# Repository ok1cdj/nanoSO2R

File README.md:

# nanoSO2R
NanoSO2R box by OK1CDJ - keep it simple stupid

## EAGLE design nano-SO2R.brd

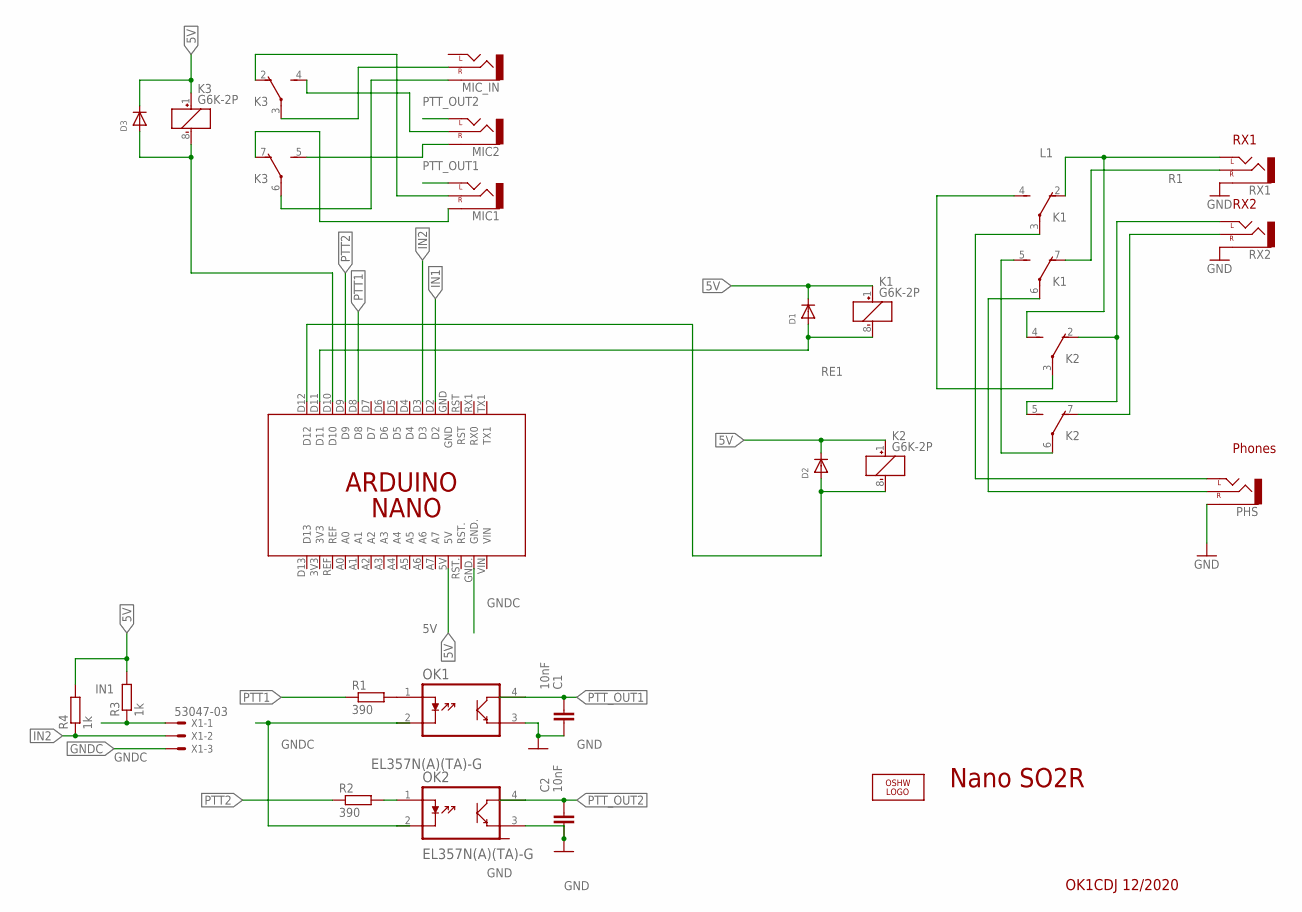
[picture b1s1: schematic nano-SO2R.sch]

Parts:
C1, C2: 10nF; C0805
D1, D2, D3: DIODESOD-323F; SOD-323F
K1, K2, K3: G6K-2P
LOGO1: OSHW_LOGO_FILLX0150-NT; OSHW_FILLX150_NOTEXT
MIC1: MIC1; AUDIO-JACK
MIC2: AUDIO-JACKPTH; AUDIO-JACK
MIC_IN: AUDIO-JACKPTH; AUDIO-JACK
OK1, OK2: EL357N(A)(TA)-G; SOP254P700X200-4N
PCB1: ARDUINO_NANO
PHS: AUDIO-JACKPTH; AUDIO-JACK
R1, R2: 390; M0805
R3, R4: 1k; M0805
RX1, RX2: AUDIO-JACKPTH; AUDIO-JACK
X1: 53047-03

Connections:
5V: D1.C, D2.C, D3.C, K1.1 (+), K2.1 (+), K3.1 (+), PCB1.5V, R3.2, R4.2
GND: C1.2, C2.2, OK1.3 (E), OK2.3 (E), PHS.SLEEVE, RX1.SLEEVE, RX2.SLEEVE
GNDC: OK1.2 (K), OK2.2 (K), PCB1.GND., X1.3
IN1: PCB1.D2, R3.1, X1.1
IN2: PCB1.D3, R4.1, X1.2
L1: K1.2 (O), K2.4 (S), RX1.TIP (LEFT)
unnamed: D3.A, K3.8 (-), PCB1.D10
unnamed: K3.3, MIC_IN.RING (RIGHT)
unnamed: K3.6, MIC_IN.SLEEVE
unnamed: K2.2 (O), K2.5 (S), RX2.TIP (LEFT)
unnamed: K2.7 (O), RX2.RING (RIGHT)
unnamed: K1.3, PHS.TIP (LEFT)
unnamed: K1.6, PHS.RING (RIGHT)
unnamed: K1.4 (S), K2.3
unnamed: K1.5 (S), K2.6
unnamed: K3.2 (O), MIC1.RING (RIGHT)
unnamed: OK2.1 (A), R2.2
unnamed: K3.7 (O), MIC1.SLEEVE
unnamed: K3.5 (S), MIC2.SLEEVE
unnamed: K3.4 (S), MIC2.RING (RIGHT)
unnamed: OK1.1 (A), R1.2
PTT1: PCB1.D8, R1.1
PTT2: PCB1.D9, R2.1
PTT_OUT1: C1.1, MIC1.TIP (LEFT), OK1.4 (C)
PTT_OUT2: C2.1, MIC2.TIP (LEFT), OK2.4 (C)
R1: K1.7 (O), RX1.RING (RIGHT)
RE1: D1.A, K1.8 (-), PCB1.D11
RE2: D2.A, K2.8 (-), PCB1.D12

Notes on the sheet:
Nano SO2R
RX2
RX1
OK1CDJ 12/2020
Phones

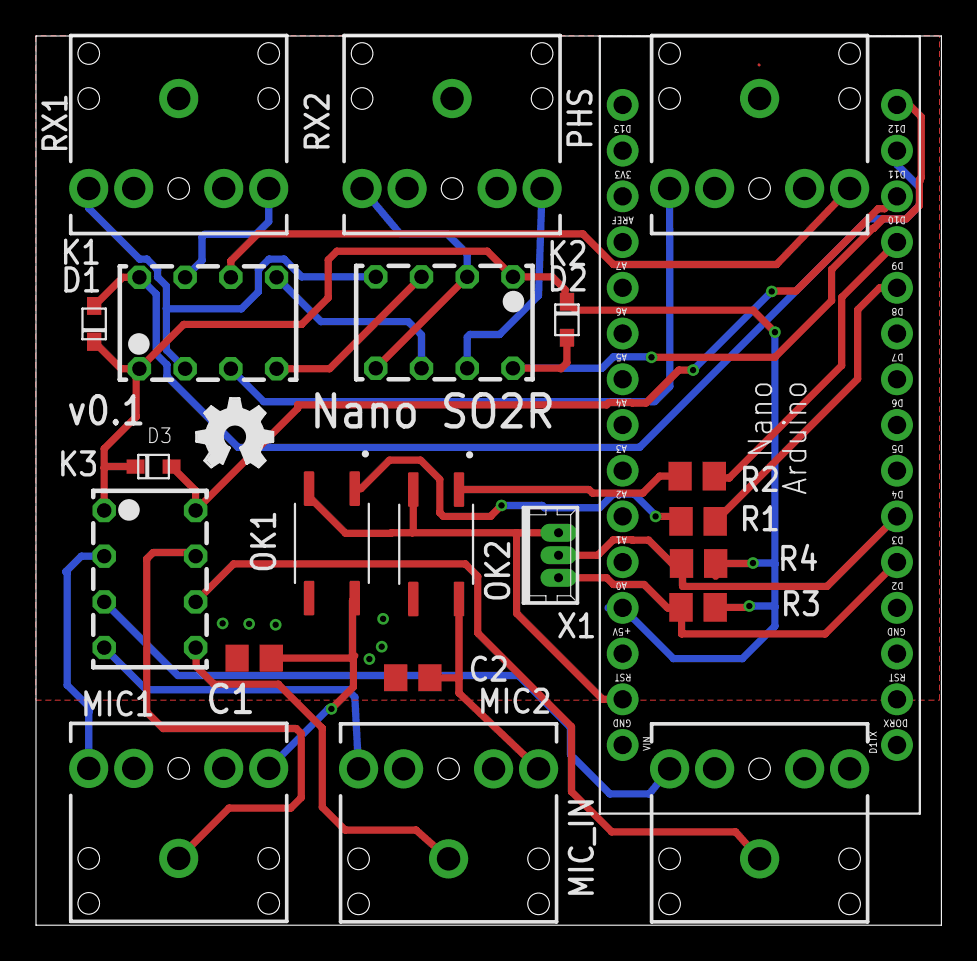
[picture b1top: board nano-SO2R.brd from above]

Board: 2 copper layers, 50.3 x 49.4 mm, 23 parts (0 on the bottom side), 28 nets.

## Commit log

2021-09-09 Arduino source code
2021-09-09 Schematic
2021-09-09 Schematic update
2021-09-09 Eagle files
